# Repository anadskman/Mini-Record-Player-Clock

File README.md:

# Mini Record Player Clock

A compact desktop Bluetooth speaker and clock inspired by a vintage record player. The aim of this project is to combine a functional Bluetooth speaker and Wi-Fi clock into a clean, fully 3D printed desktop display. Rather than using lots of jumper wires and modules glued together, everything is connected through a custom PCB designed specifically for this project.

The record spins while music is playing, the tonearm moves using a servo, and the front display shows the current time synced over Wi-Fi. All electronics are housed inside a custom enclosure designed in Fusion 360.

## Features

- Bluetooth music playback
- Wi-Fi synced digital clock
- 2.4" ILI9341 colour TFT display
- Spinning 3D printed record
- Servo driven moving tonearm
- Physical playback buttons
- Custom PCB
- Fully 3D printed enclosure
- Powered by a 5V wall adapter

## Hardware

### Electronics

- ESP32 Dev Board
- 2.4" ILI9341 TFT Display
- PAM8403 Audio Amplifier
- 4Ω 3W Speaker
- 5V DC Motor
- SG90 Servo
- IRLZ44N MOSFET
- 1N5819 Diodes
- Push Buttons
- LEDs
- Capacitors and Resistors
- Custom PCB

### Mechanical

- Fully 3D printed enclosure
- 3D printed record
- 3D printed tonearm
- Motor mount
- Hinged lid
- PCB mounting system
- M2 hardware

## Software

The ESP32 is responsible for controlling the entire project. It handles Bluetooth audio, synchronises the clock over Wi-Fi, updates the display, controls the spinning record and tonearm, and reads the playback buttons.

The firmware is written using the Arduino framework and is designed so each part of the project works independently while sharing the same controller.

## PCB

A custom two-layer PCB was designed in KiCad to act as the hub of the project. All components connect directly to the PCB which keeps the wiring simple and makes assembly much cleaner.

Some design considerations included:

- Ground planes on both PCB layers
- Wider traces for power distribution
- Decoupling capacitors placed beside each module
- Reverse polarity protection
- Clearly labelled connectors
- Connectors for external buttons, speaker and servo
- Mounting holes for the enclosure

## CAD

The enclosure was designed in Fusion 360 around the PCB to ensure everything fits correctly.

The design includes:

- Front display opening
- Side mounted playback buttons
- Speaker openings
- Hinged top lid
- Motor mount
- Servo mount
- PCB mounting points
- Rear barrel jack opening

## BOM

| Component | Cost | Status |
|---|---:|---|
| TFT Display 2.4" ILI9341 | $4.01 | Buy |
| 4Ω 3W Speaker | $2.09 | Buy |
| Screw Terminal (7x) | Owned | Owned |
| DC Barrel Jack | Owned | Owned |
| LEDs (2x) | Owned | Owned |
| MOSFET | Owned | Owned |
| Header Pins | Owned | Owned |
| PAM8403 Amplifier Module | $4.02 | Buy |
| DC Motor | Owned | Owned |
| SG90 Servo Motor | Owned | Owned |
| 100µF Capacitors | Owned | Owned |
| 100nF Ceramic Capacitors | Owned | Owned |
| 470µF Capacitor | $8.65 | Buy |
| 10µF Capacitors | $2.13 | Buy |
| 1µF Capacitors | $2.08 | Buy |
| Resistors | Owned | Owned |
| 1N5819 Diodes | $4.35 | Buy |
| Push Buttons | Owned | Owned |
| ESP32 Dev Board | $4.40 | Buy |
| 5V 5A Barrel Jack Power Supply | $9.43 | Buy |
| PCB | $27.77 | Buy |
| M2 Screws | $5.40 | Buy |
| Pin Headers (ESP32) | $6.06 | Buy |
| Shipping | $1.63 | |
| Duties | $33.01 | |
| Total | $115.03 | |

## Images
| Schematic | PCB | CAD |
| :---: | :---: | :---: |
|  |  |  |

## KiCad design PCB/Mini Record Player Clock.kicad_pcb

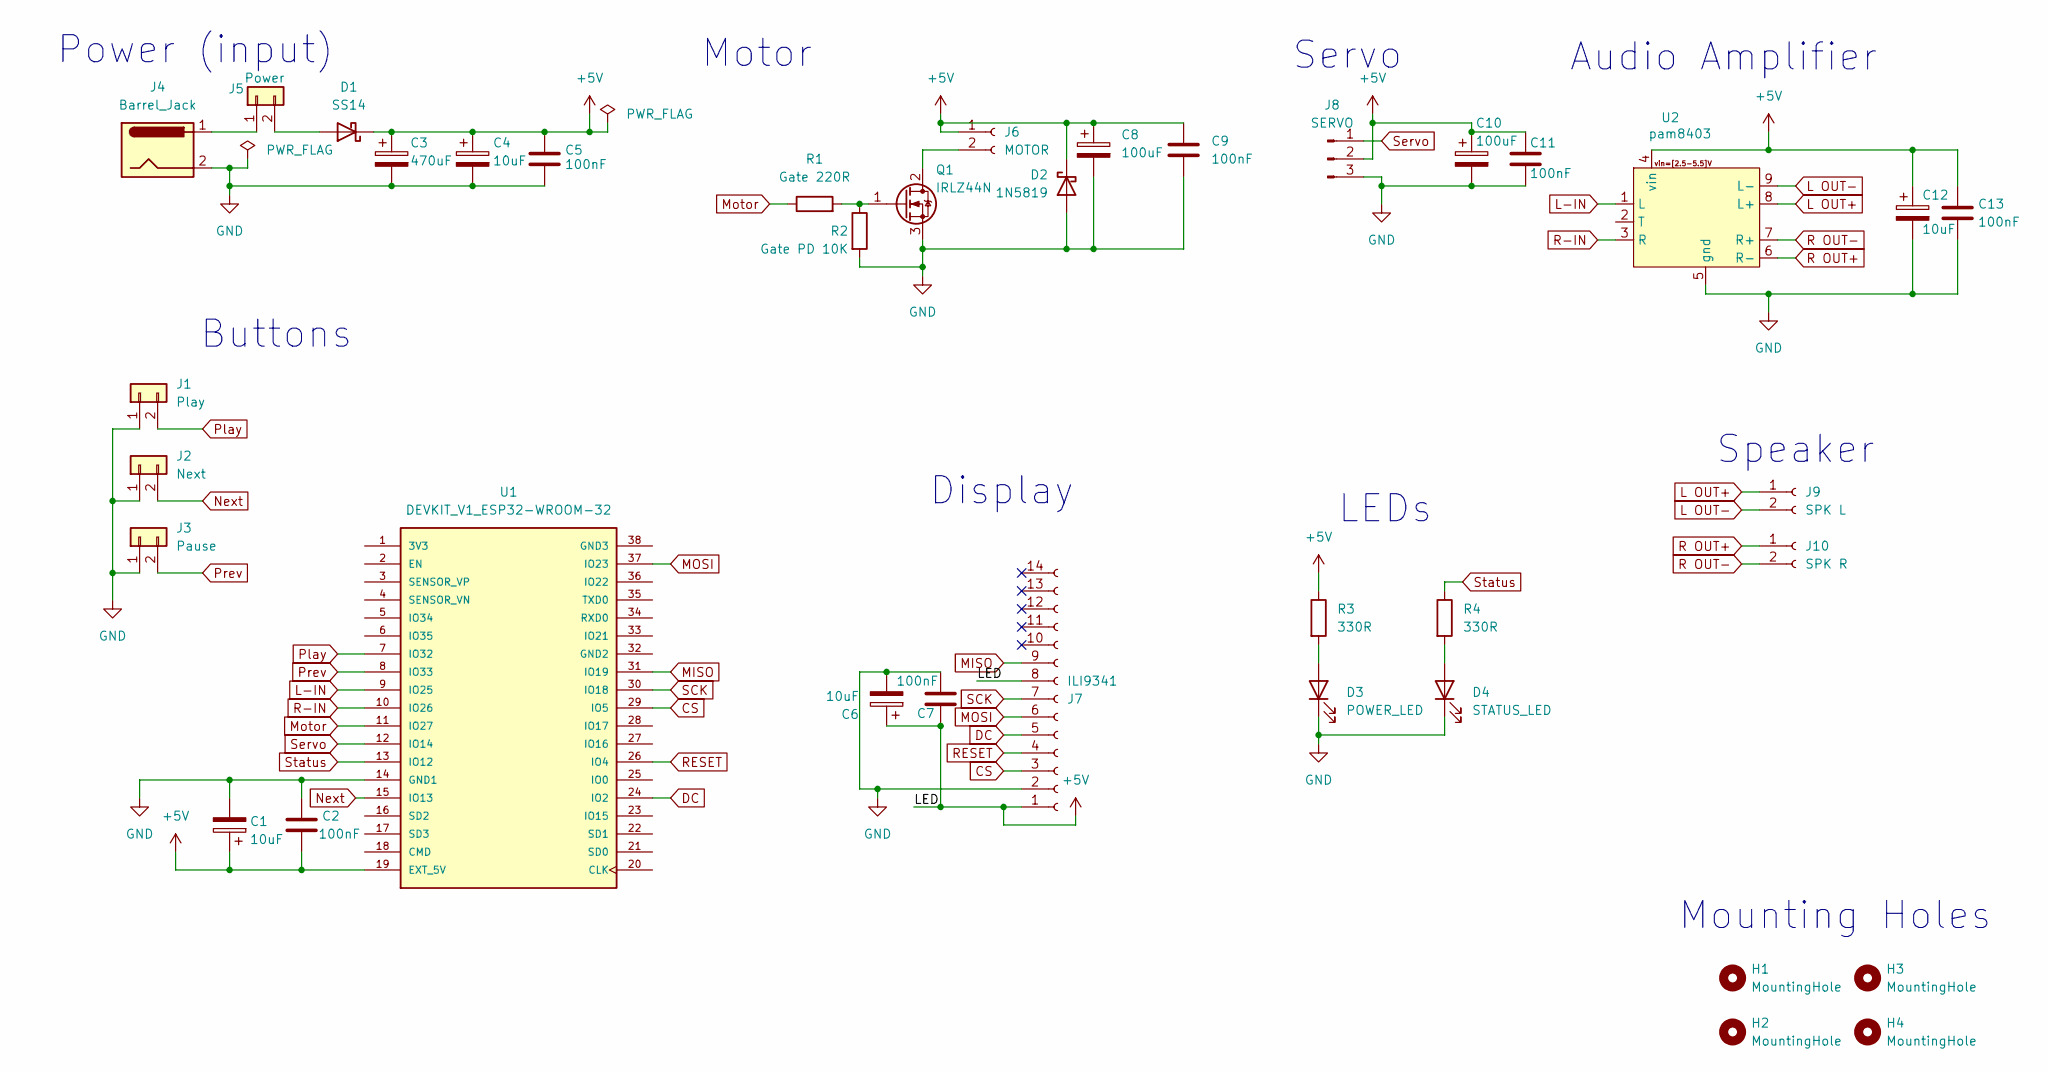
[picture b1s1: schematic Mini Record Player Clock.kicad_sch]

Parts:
C1, C4, C6, C12: 10uF; CP_Radial_D5.0mm_P2.00mm
C2, C5, C7, C9, C11, C13: 100nF; C_Disc_D5.0mm_W2.5mm_P5.00mm
C3: 470uF; CP_Radial_D8.0mm_P3.50mm
C8, C10: 100uF; CP_Radial_D6.3mm_P2.50mm
D1: SS14; D_DO-41_SOD81_P10.16mm_Horizontal
D2: 1N5819; D_DO-41_SOD81_P10.16mm_Horizontal
D3: POWER_LED; LED_D5.0mm
D4: STATUS_LED; LED_D5.0mm
H1, H2, H3, H4: MountingHole; MountingHole_3.2mm_M3
J1: Play; TerminalBlock_Phoenix_MPT-0,5-2-2.54_1x02_P2.54mm_Horizontal
J2: Next; TerminalBlock_Phoenix_MPT-0,5-2-2.54_1x02_P2.54mm_Horizontal
J3: Pause; TerminalBlock_Phoenix_MPT-0,5-2-2.54_1x02_P2.54mm_Horizontal
J4: Barrel_Jack; BarrelJack_Horizontal
J5: Power; TerminalBlock_Phoenix_MPT-0,5-2-2.54_1x02_P2.54mm_Horizontal
J6: MOTOR; TerminalBlock_Phoenix_MPT-0,5-2-2.54_1x02_P2.54mm_Horizontal
J7: ILI9341; PinHeader_1x14_P2.54mm_Vertical
J8: SERVO; PinHeader_1x03_P2.54mm_Vertical
J9: SPK L; TerminalBlock_Phoenix_MPT-0,5-2-2.54_1x02_P2.54mm_Horizontal
J10: SPK R; TerminalBlock_Phoenix_MPT-0,5-2-2.54_1x02_P2.54mm_Horizontal
Q1: IRLZ44N; TO-220-3_Vertical
R1: Gate 220R; R_Axial_DIN0207_L6.3mm_D2.5mm_P10.16mm_Horizontal
R2: Gate PD 10K; R_Axial_DIN0207_L6.3mm_D2.5mm_P10.16mm_Horizontal
R3, R4: 330R; R_Axial_DIN0207_L6.3mm_D2.5mm_P10.16mm_Horizontal
U1: DEVKIT_V1_ESP32-WROOM-32; MODULE_DEVKIT_V1_ESP32-WROOM-32; PARTREV N/A
U2: pam8403

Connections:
+5V: C1.1, C2.2, C3.1, C4.1, C5.1, C6.1, C7.1, C8.1, C9.1, C10.1, C11.1, C12.1, C13.1, D1.1 (K), D2.1 (K), J6.1, J7.1, J7.8, J8.2, R3.1, U1.19 (EXT_5V), U2.4 (vin)
CS: J7.3, U1.29 (IO5)
DC: J7.5, U1.24 (IO2)
GND: C1.2, C2.1, C3.2, C4.2, C5.2, C6.2, C7.2, C8.2, C9.2, C10.2, C11.2, C12.2, C13.2, D2.2 (A), D3.1 (K), D4.1 (K), J1.1, J2.1, J3.1, J4.2, J7.2, J8.3, Q1.3 (S), R2.2, U1.14 (GND1), U2.5 (gnd)
L OUT+: J9.1, U2.8 (L+)
L OUT-: J9.2, U2.9 (L-)
L-IN: U1.9 (IO25), U2.1 (L)
MISO: J7.9, U1.31 (IO19)
MOSI: J7.6, U1.37 (IO23)
Motor: R1.1, U1.11 (IO27)
unnamed: D1.2 (A), J5.2
unnamed: D3.2 (A), R3.2
unnamed: D4.2 (A), R4.2
unnamed: J4.1, J5.1
unnamed: J6.2, Q1.2 (D)
unnamed: Q1.1 (G), R1.2, R2.1
Next: J2.2, U1.15 (IO13)
Play: J1.2, U1.7 (IO32)
Prev: J3.2, U1.8 (IO33)
R OUT+: J10.1, U2.6 (R-)
R OUT-: J10.2, U2.7 (R+)
R-IN: U1.10 (IO26), U2.3 (R)
RESET: J7.4, U1.26 (IO4)
SCK: J7.7, U1.30 (IO18)
Servo: J8.1, U1.12 (IO14)
Status: R4.1, U1.13 (IO12)

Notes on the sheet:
Display
Mounting Holes
Audio Amplifier
LEDs
Speaker
Power (input)
Motor
Buttons
Servo

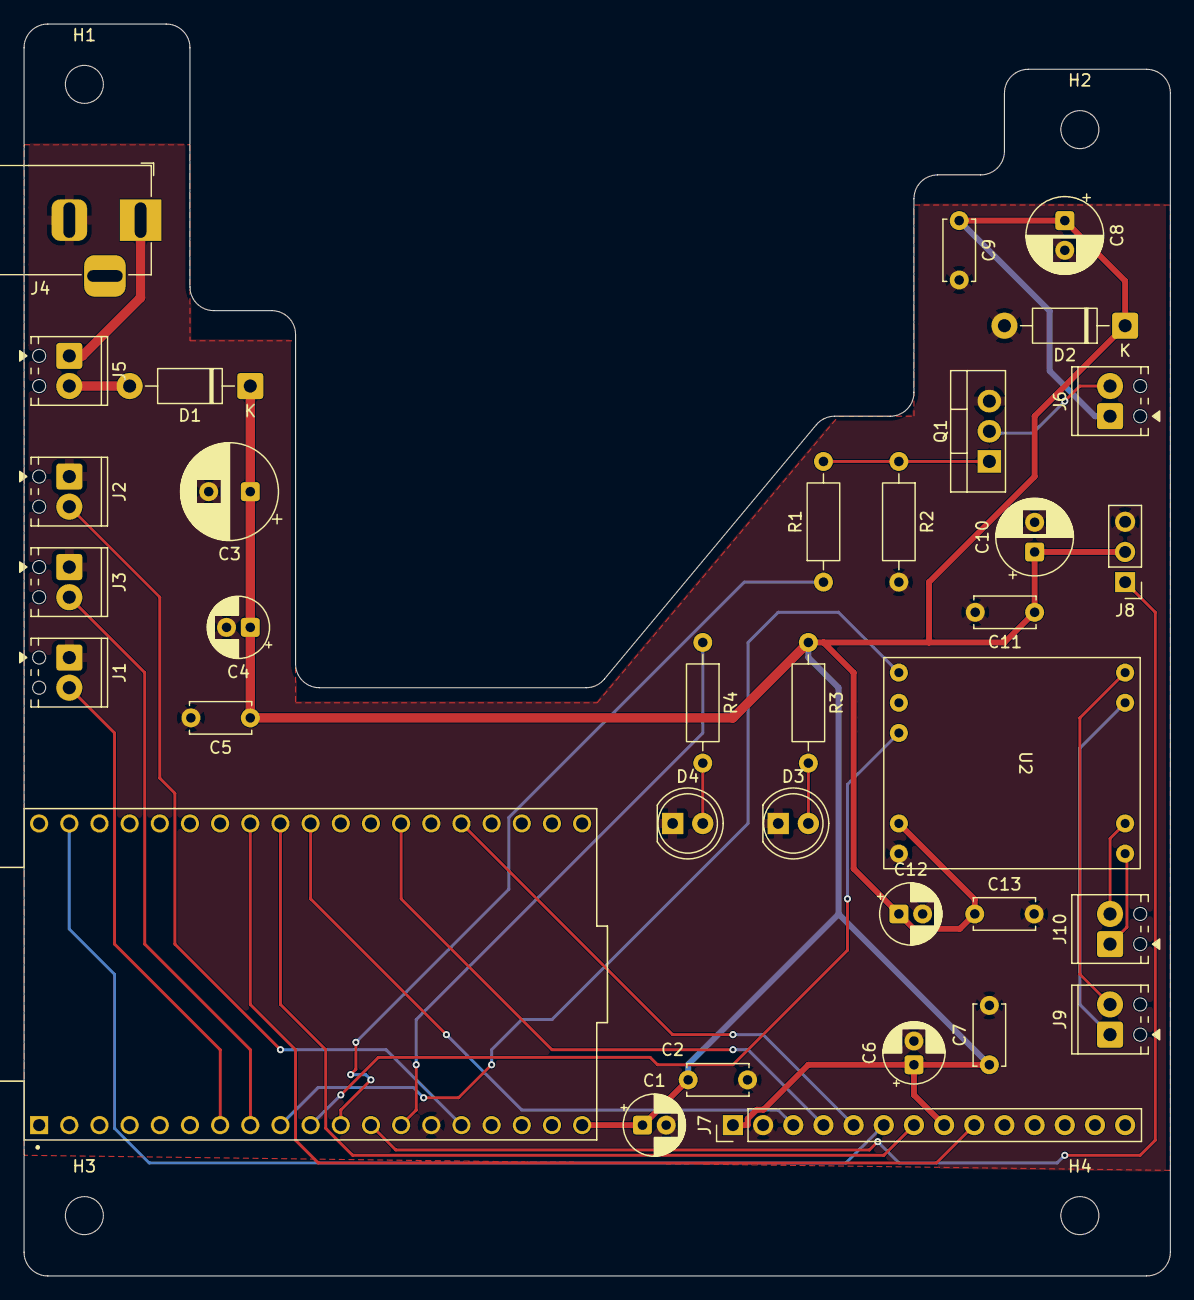
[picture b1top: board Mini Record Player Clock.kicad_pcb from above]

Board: 2 copper layers, 96.5 x 105.4 mm, 38 parts (0 on the bottom side), 26 nets.
